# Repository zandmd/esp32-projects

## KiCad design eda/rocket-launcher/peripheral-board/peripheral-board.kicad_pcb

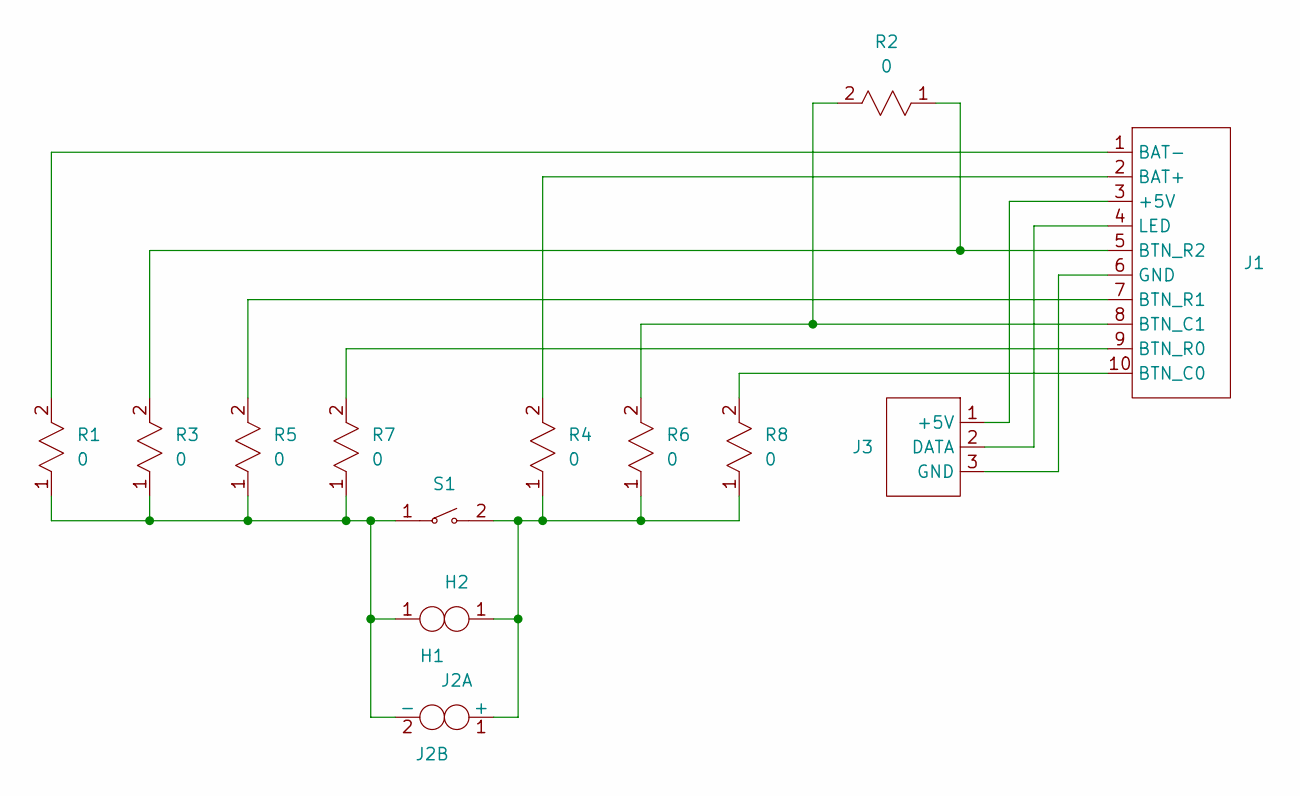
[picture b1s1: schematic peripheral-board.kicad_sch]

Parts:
H1, H2: B076FX76R8
J1: 302-S101
J2: B095WMQ8Y8
J3: B01AG923GI
R1, R2, R3, R4, R5, R6, R7, R8: 0; PASSIVE-NPOL-0805
S1: B07QKFD7Z7

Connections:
unnamed: J1.1 (BAT-), R1.2
unnamed: J1.2 (BAT+), R4.2
unnamed: J1.3 (+5V), J3.1 (+5V)
unnamed: J1.4 (LED), J3.2 (DATA)
unnamed: J1.5 (BTN_R2), R2.1, R3.2
unnamed: J1.6 (GND), J3.3 (GND)
unnamed: J1.7 (BTN_R1), R5.2
unnamed: J1.8 (BTN_C1), R2.2, R6.2
unnamed: J1.9 (BTN_R0), R7.2
unnamed: J1.10 (BTN_C0), R8.2
unnamed: H2.1, J2.1 (+), R4.1, R6.1, R8.1, S1.2
unnamed: H1.1, J2.2 (-), R1.1, R3.1, R5.1, R7.1, S1.1

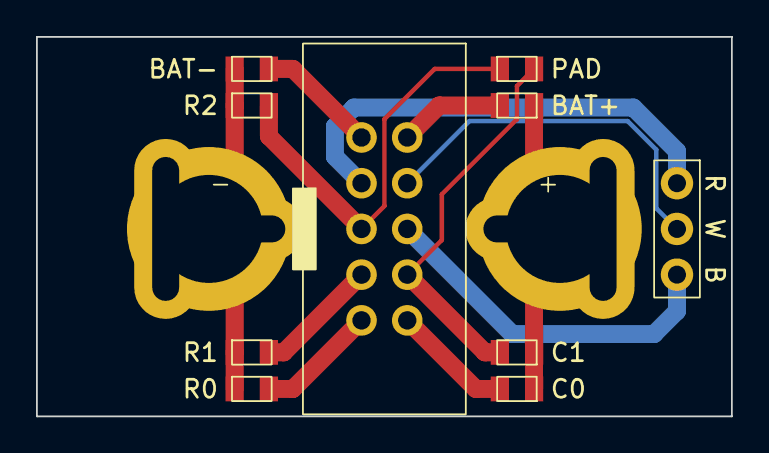
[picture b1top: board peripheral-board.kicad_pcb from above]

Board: 2 copper layers, 38.6 x 21.1 mm, 14 parts (0 on the bottom side), 12 nets.

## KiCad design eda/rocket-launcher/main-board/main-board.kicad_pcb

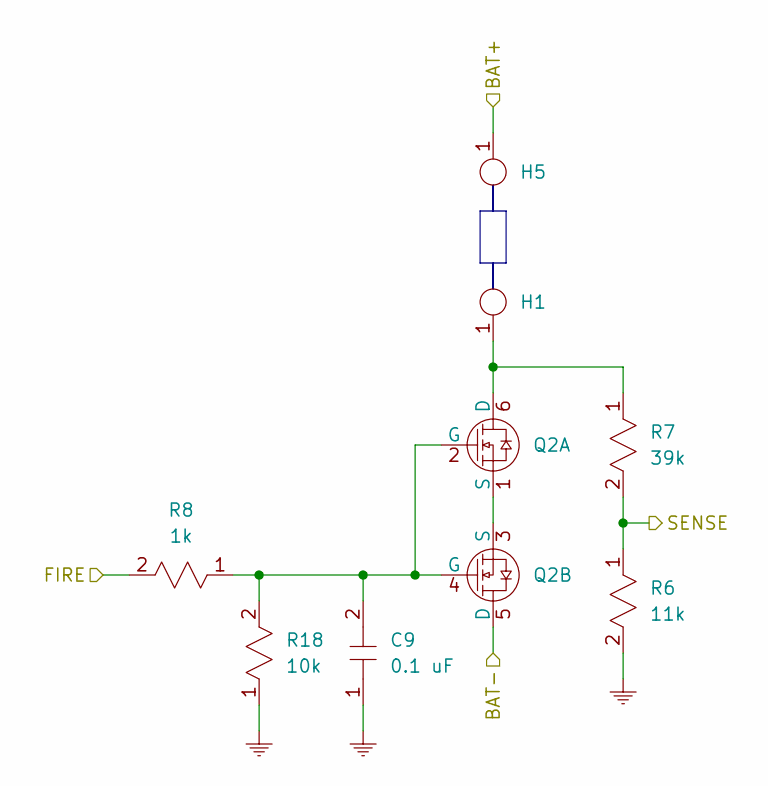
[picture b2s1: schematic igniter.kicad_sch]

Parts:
C9: 0.1 uF; PASSIVE-NPOL-0805
H1, H5: B076FX76R8
Q2: G120N03D32
R6: 11k; PASSIVE-NPOL-0805
R7: 39k; PASSIVE-NPOL-0805
R8: 1k; PASSIVE-NPOL-0805
R18: 10k; PASSIVE-NPOL-0805

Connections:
/+: H5.1; also elsewhere on the board
/-: Q2.5 (D); also elsewhere on the board
/Igniter0/FIRE: R8.2; also elsewhere on the board
/Igniter0/SENSE: R6.1, R7.2; also elsewhere on the board
GND: C9.1, R6.2, R18.1; also elsewhere on the board
unnamed: H1.1, Q2.6 (D), R7.1
unnamed: C9.2, Q2.2 (G), Q2.4 (G), R8.1, R18.2
unnamed: Q2.1 (S), Q2.3 (S)

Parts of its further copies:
C10, C11, C13: 0.1 uF; PASSIVE-NPOL-0805
H2, H3, H4, H6, H7, H8: B076FX76R8
Q3, Q4, Q5: G120N03D32
R9, R12, R15: 11k; PASSIVE-NPOL-0805
R10, R13, R16: 39k; PASSIVE-NPOL-0805
R11, R14, R17: 1k; PASSIVE-NPOL-0805
R19, R20, R21: 10k; PASSIVE-NPOL-0805

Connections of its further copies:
/+: H6.1, H7.1, H8.1; also elsewhere on the board
/-: Q3.5 (D), Q4.5 (D), Q5.5 (D); also elsewhere on the board
/Igniter1/FIRE: R14.2; also elsewhere on the board
/Igniter1/SENSE: R12.1, R13.2; also elsewhere on the board
/Igniter2/FIRE: R11.2; also elsewhere on the board
/Igniter2/SENSE: R9.1, R10.2; also elsewhere on the board
/Igniter3/FIRE: R17.2; also elsewhere on the board
/Igniter3/SENSE: R15.1, R16.2; also elsewhere on the board
GND: C10.1, C11.1, C13.1, R9.2, R12.2, R15.2, R19.1, R20.1, R21.1; also elsewhere on the board
unnamed: H2.1, Q3.6 (D), R10.1
unnamed: C10.2, Q3.2 (G), Q3.4 (G), R11.1, R19.2
unnamed: Q3.1 (S), Q3.3 (S)
unnamed: H3.1, Q4.6 (D), R13.1
unnamed: C11.2, Q4.2 (G), Q4.4 (G), R14.1, R20.2
unnamed: Q4.1 (S), Q4.3 (S)
unnamed: H4.1, Q5.6 (D), R16.1
unnamed: C13.2, Q5.2 (G), Q5.4 (G), R17.1, R21.2
unnamed: Q5.1 (S), Q5.3 (S)

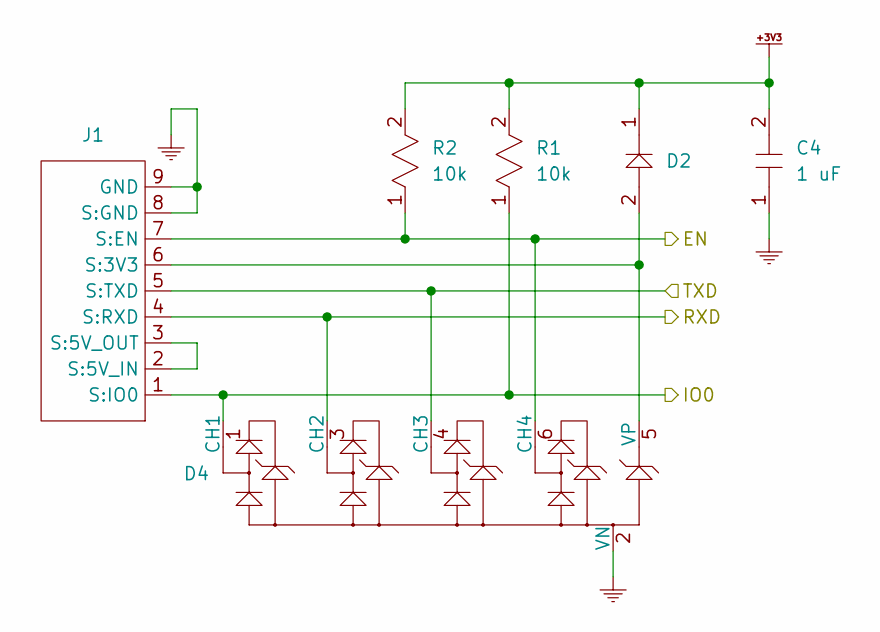
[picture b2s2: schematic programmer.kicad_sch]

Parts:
C4: 1 uF; PASSIVE-NPOL-0805
D2: PASSIVE-POL-0805
D4: CM1293A-04SO
J1: CF25081D0R0-10-NH
R1, R2: 10k; PASSIVE-NPOL-0805

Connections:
+3V3: C4.2, D2.1, R1.2, R2.2; also elsewhere on the board
/Microcontroller/EN: D4.6 (CH4), J1.7 (S:EN), R2.1; also elsewhere on the board
/Microcontroller/IO0: D4.1 (CH1), J1.1 (S:IO0), R1.1; also elsewhere on the board
/Microcontroller/RXD: D4.3 (CH2), J1.4 (S:RXD); also elsewhere on the board
/Microcontroller/TXD: D4.4 (CH3), J1.5 (S:TXD); also elsewhere on the board
GND: C4.1, D4.2 (VN), J1.8 (S:GND), J1.9 (GND); also elsewhere on the board
unnamed: D2.2, D4.5 (VP), J1.6 (S:3V3)
unnamed: J1.2 (S:5V_IN), J1.3 (S:5V_OUT)

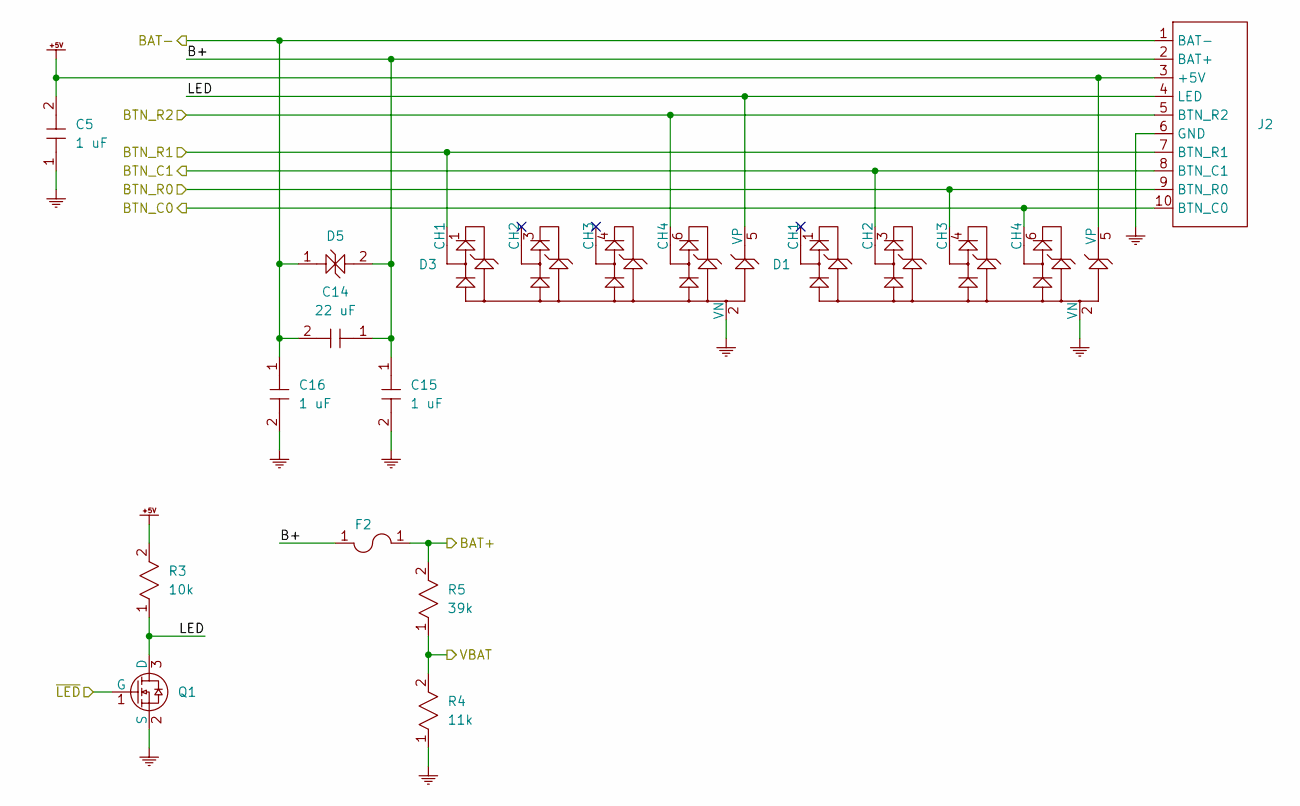
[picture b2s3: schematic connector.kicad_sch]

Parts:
C5, C15, C16: 1 uF; PASSIVE-NPOL-0805
C14: 22 uF; PASSIVE-NPOL-0805
D1, D3: CM1293A-04SO
D5: SMAJ15CA
F2, F3: 3586KTR
J2: 302-S101
Q1: BSS816NWH6327XTSA1
R3: 10k; PASSIVE-NPOL-0805
R4: 11k; PASSIVE-NPOL-0805
R5: 39k; PASSIVE-NPOL-0805

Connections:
+5V: C5.2, D1.5 (VP), J2.3 (+5V), R3.2; also elsewhere on the board
/+: F3.1, R5.2; also elsewhere on the board
/-: C14.2, C16.1, D5.1, J2.1 (BAT-); also elsewhere on the board
/Connector/B+: C14.1, C15.1, D5.2, F2.1, J2.2 (BAT+)
/Connector/BTN_C0: D1.6 (CH4), J2.10 (BTN_C0); also elsewhere on the board
/Connector/BTN_C1: D1.3 (CH2), J2.8 (BTN_C1); also elsewhere on the board
/Connector/BTN_R0: D1.4 (CH3), J2.9 (BTN_R0); also elsewhere on the board
/Connector/BTN_R1: D3.1 (CH1), J2.7 (BTN_R1); also elsewhere on the board
/Connector/BTN_R2: D3.6 (CH4), J2.5 (BTN_R2); also elsewhere on the board
/Connector/LED: D3.5 (VP), J2.4 (LED), Q1.3 (D), R3.1
/Connector/VBAT: R4.2, R5.1; also elsewhere on the board
/Connector/~LED: Q1.1 (G); also elsewhere on the board
GND: C5.1, C15.2, C16.2, D1.2 (VN), D3.2 (VN), J2.6 (GND), Q1.2 (S), R4.1; also elsewhere on the board

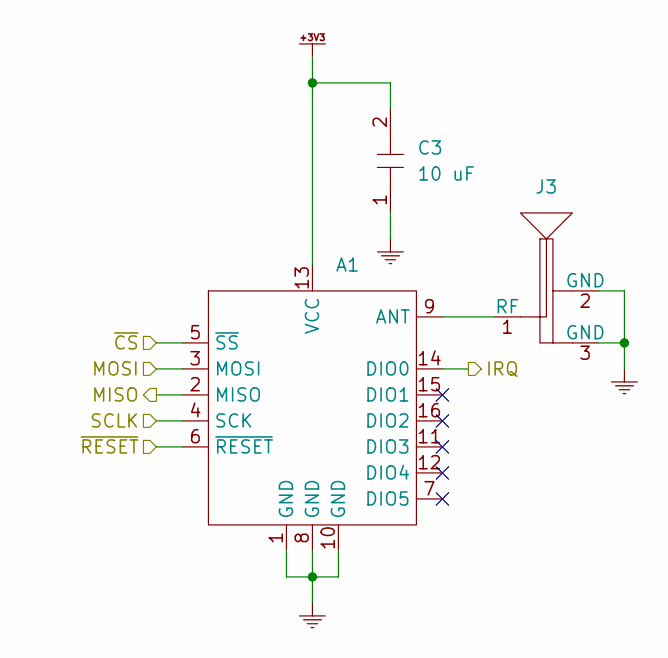
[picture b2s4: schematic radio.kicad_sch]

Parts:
A1: 5684
C3: 10 uF; PASSIVE-NPOL-0805
J3: 2337019-1

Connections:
+3V3: A1.13 (VCC), C3.2; also elsewhere on the board
/Microcontroller/MISO: A1.2 (MISO); also elsewhere on the board
/Microcontroller/MOSI: A1.3 (MOSI); also elsewhere on the board
/Microcontroller/RFM_IRQ: A1.14 (DIO0); also elsewhere on the board
/Microcontroller/SCLK: A1.4 (SCK); also elsewhere on the board
/Microcontroller/~CS: A1.5 (~SS); also elsewhere on the board
/Microcontroller/~RFM_RST: A1.6 (~RESET); also elsewhere on the board
GND: A1.1 (GND), A1.8 (GND), A1.10 (GND), C3.1, J3.2 (GND), J3.3 (GND); also elsewhere on the board
unnamed: A1.9 (ANT), J3.1 (RF)

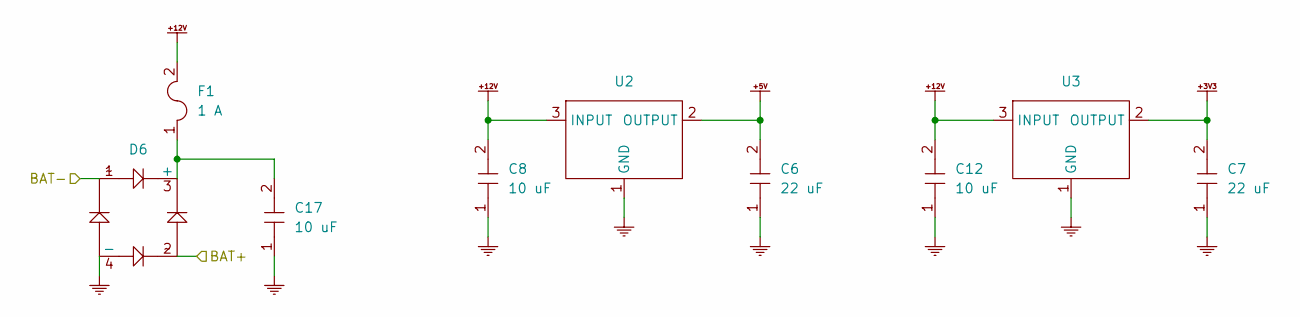
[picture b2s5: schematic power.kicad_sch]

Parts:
C6, C7: 22 uF; PASSIVE-NPOL-0805
C8, C12, C17: 10 uF; PASSIVE-NPOL-0805
D6: MB14S
F1: 1 A; PASSIVE-NPOL-1206
U2: AZ1117IH-5.0TRG1
U3: AZ1117IH-3.3TRG1

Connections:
+3V3: C7.2, U3.2 (OUTPUT); also elsewhere on the board
+5V: C6.2, U2.2 (OUTPUT); also elsewhere on the board
+12V: C8.2, C12.2, F1.2, U2.3 (INPUT), U3.3 (INPUT)
/+: D6.2; also elsewhere on the board
/-: D6.1; also elsewhere on the board
GND: C6.1, C7.1, C8.1, C12.1, C17.1, D6.4 (-), U2.1 (GND), U3.1 (GND); also elsewhere on the board
unnamed: C17.2, D6.3 (+), F1.1

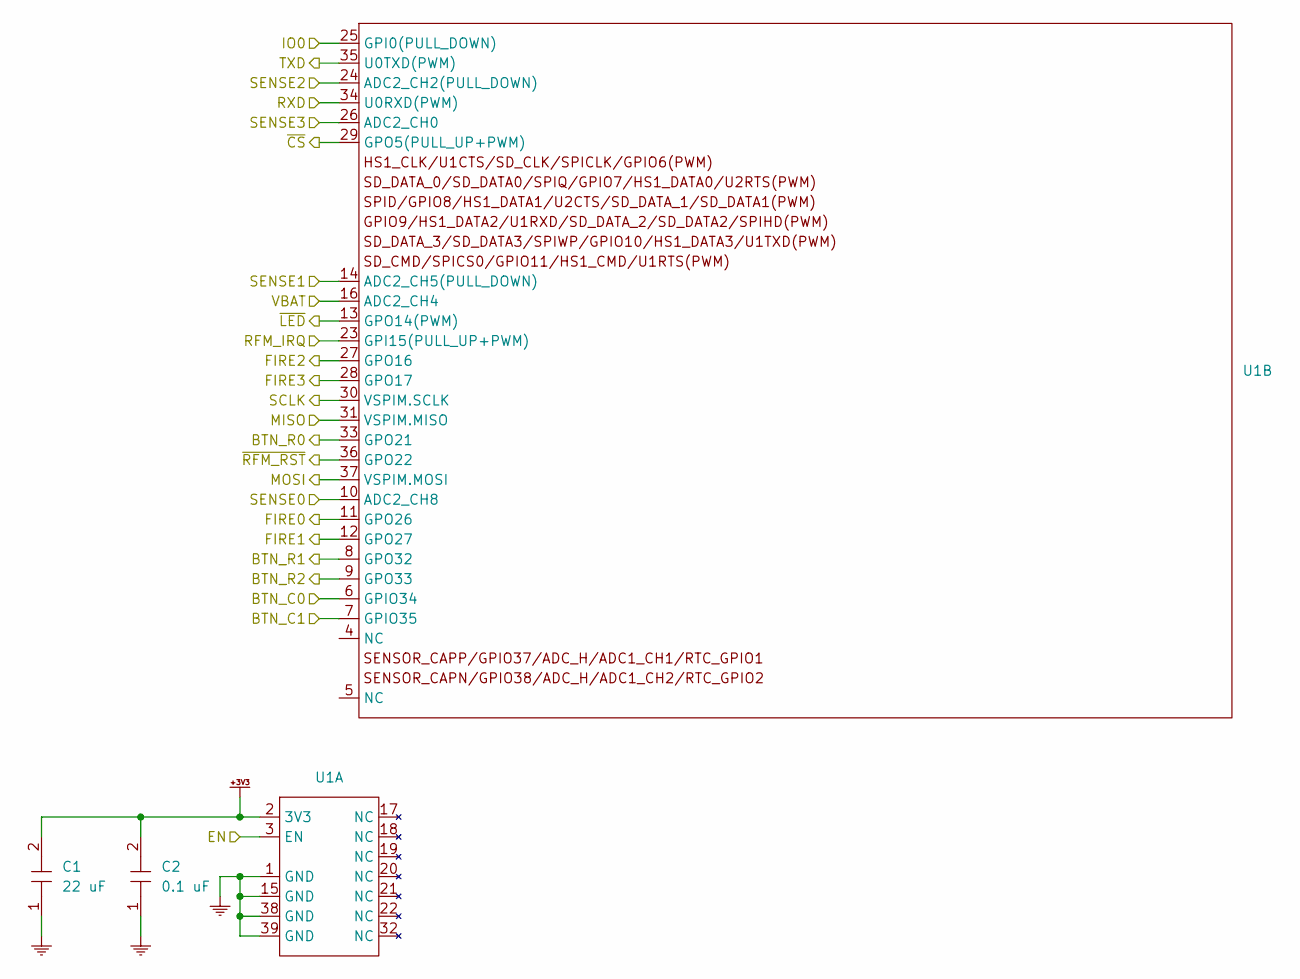
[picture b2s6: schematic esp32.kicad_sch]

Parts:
C1: 22 uF; PASSIVE-NPOL-0805
C2: 0.1 uF; PASSIVE-NPOL-0805
U1: ESP32-WROOM-32E-N4

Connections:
+3V3: C1.2, C2.2, U1.2 (3V3); also elsewhere on the board
/Connector/BTN_C0: U1.6 (GPIO34); also elsewhere on the board
/Connector/BTN_C1: U1.7 (GPIO35); also elsewhere on the board
/Connector/BTN_R0: U1.33 (GPO21); also elsewhere on the board
/Connector/BTN_R1: U1.8 (GPO32); also elsewhere on the board
/Connector/BTN_R2: U1.9 (GPO33); also elsewhere on the board
/Connector/VBAT: U1.16 (ADC2_CH4); also elsewhere on the board
/Connector/~LED: U1.13 (GPO14(PWM)); also elsewhere on the board
/Igniter0/FIRE: U1.11 (GPO26); also elsewhere on the board
/Igniter0/SENSE: U1.10 (ADC2_CH8); also elsewhere on the board
/Igniter1/FIRE: U1.12 (GPO27); also elsewhere on the board
/Igniter1/SENSE: U1.14 (ADC2_CH5(PULL_DOWN)); also elsewhere on the board
/Igniter2/FIRE: U1.27 (GPO16); also elsewhere on the board
/Igniter2/SENSE: U1.24 (ADC2_CH2(PULL_DOWN)); also elsewhere on the board
/Igniter3/FIRE: U1.28 (GPO17); also elsewhere on the board
/Igniter3/SENSE: U1.26 (ADC2_CH0); also elsewhere on the board
/Microcontroller/EN: U1.3 (EN); also elsewhere on the board
/Microcontroller/IO0: U1.25 (GPI0(PULL_DOWN)); also elsewhere on the board
/Microcontroller/MISO: U1.31 (VSPIM.MISO); also elsewhere on the board
/Microcontroller/MOSI: U1.37 (VSPIM.MOSI); also elsewhere on the board
/Microcontroller/RFM_IRQ: U1.23 (GPI15(PULL_UP+PWM)); also elsewhere on the board
/Microcontroller/RXD: U1.34 (U0RXD(PWM)); also elsewhere on the board
/Microcontroller/SCLK: U1.30 (VSPIM.SCLK); also elsewhere on the board
/Microcontroller/TXD: U1.35 (U0TXD(PWM)); also elsewhere on the board
/Microcontroller/~CS: U1.29 (GPO5(PULL_UP+PWM)); also elsewhere on the board
/Microcontroller/~RFM_RST: U1.36 (GPO22); also elsewhere on the board
GND: C1.1, C2.1, U1.1 (GND), U1.15 (GND), U1.38 (GND), U1.39 (GND); also elsewhere on the board

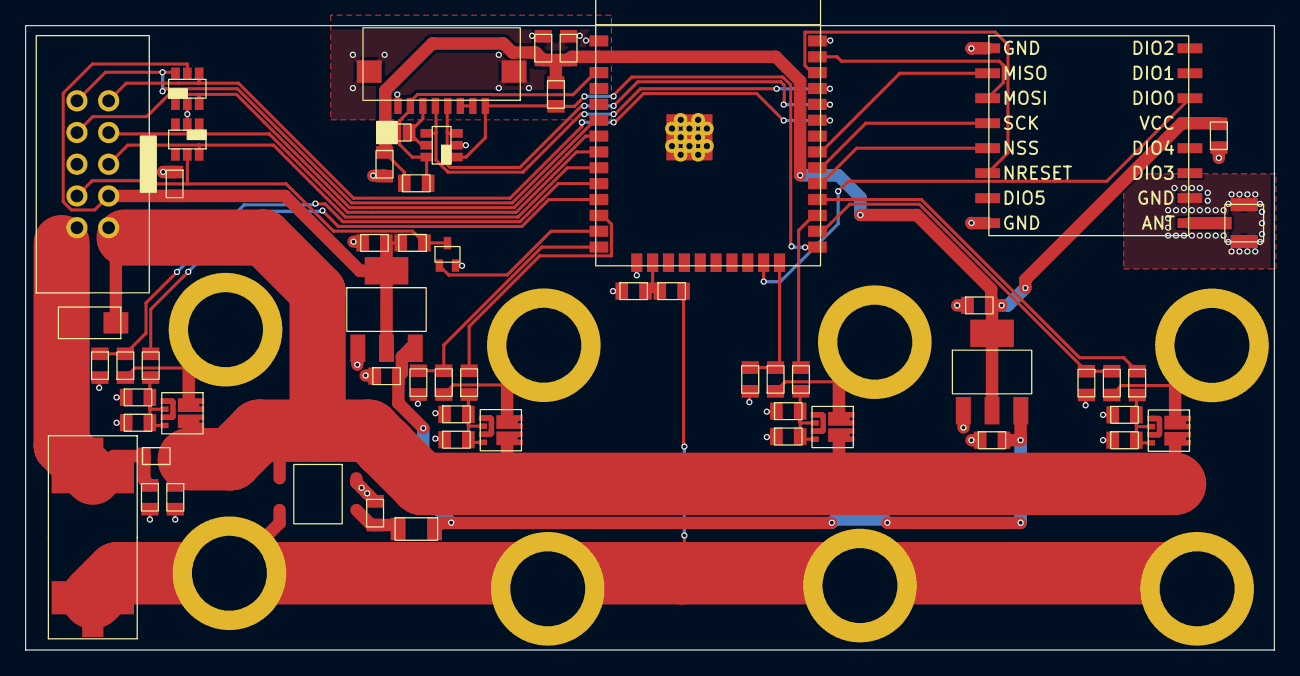
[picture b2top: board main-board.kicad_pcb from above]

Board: 2 copper layers, 100.0 x 50.0 mm, 67 parts (0 on the bottom side), 49 nets.

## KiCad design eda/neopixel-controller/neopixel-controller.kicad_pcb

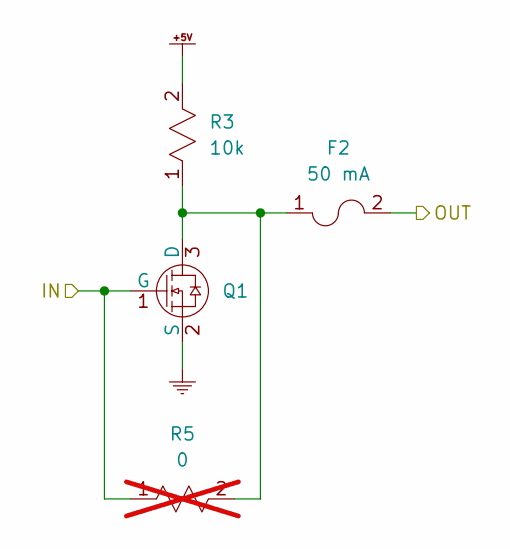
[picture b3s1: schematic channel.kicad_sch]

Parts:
F2: 50 mA; PASSIVE-NPOL-1206
Q1: BSS816NWH6327XTSA1
R3: 10k; PASSIVE-NPOL-0805
R5: 0; PASSIVE-NPOL-0805; not fitted

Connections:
+5V: R3.2; also elsewhere on the board
/Channel 0/IN: Q1.1 (G), R5.1; also elsewhere on the board
/Channel 0/OUT: F2.2; also elsewhere on the board
GND: Q1.2 (S); also elsewhere on the board
unnamed: F2.1, Q1.3 (D), R3.1, R5.2

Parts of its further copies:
F3, F4, F5, F6, F7, F8, F9: 50 mA; PASSIVE-NPOL-1206
Q2, Q3, Q4, Q5, Q6, Q7, Q8: BSS816NWH6327XTSA1
R4, R7, R9, R11, R13, R17, R18: 10k; PASSIVE-NPOL-0805
R6, R8, R10, R14, R15, R19, R20: 0; PASSIVE-NPOL-0805; not fitted

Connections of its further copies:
+5V: R4.2, R7.2, R9.2, R11.2, R13.2, R17.2, R18.2; also elsewhere on the board
/Channel 1/IN: Q2.1 (G), R6.1; also elsewhere on the board
/Channel 1/OUT: F3.2; also elsewhere on the board
/Channel 2/IN: Q4.1 (G), R10.1; also elsewhere on the board
/Channel 2/OUT: F4.2; also elsewhere on the board
/Channel 3/IN: Q3.1 (G), R8.1; also elsewhere on the board
/Channel 3/OUT: F5.2; also elsewhere on the board
/Channel 4/IN: Q6.1 (G), R15.1; also elsewhere on the board
/Channel 4/OUT: F6.2; also elsewhere on the board
/Channel 5/IN: Q5.1 (G), R14.1; also elsewhere on the board
/Channel 5/OUT: F7.2; also elsewhere on the board
/Channel 6/IN: Q8.1 (G), R20.1; also elsewhere on the board
/Channel 6/OUT: F8.2; also elsewhere on the board
/Channel 7/IN: Q7.1 (G), R19.1; also elsewhere on the board
/Channel 7/OUT: F9.2; also elsewhere on the board
GND: Q2.2 (S), Q3.2 (S), Q4.2 (S), Q5.2 (S), Q6.2 (S), Q7.2 (S), Q8.2 (S); also elsewhere on the board
unnamed: F3.1, Q2.3 (D), R4.1, R6.2
unnamed: F5.1, Q3.3 (D), R7.1, R8.2
unnamed: F4.1, Q4.3 (D), R9.1, R10.2
unnamed: F7.1, Q5.3 (D), R11.1, R14.2
unnamed: F6.1, Q6.3 (D), R13.1, R15.2
unnamed: F9.1, Q7.3 (D), R17.1, R19.2
unnamed: F8.1, Q8.3 (D), R18.1, R20.2

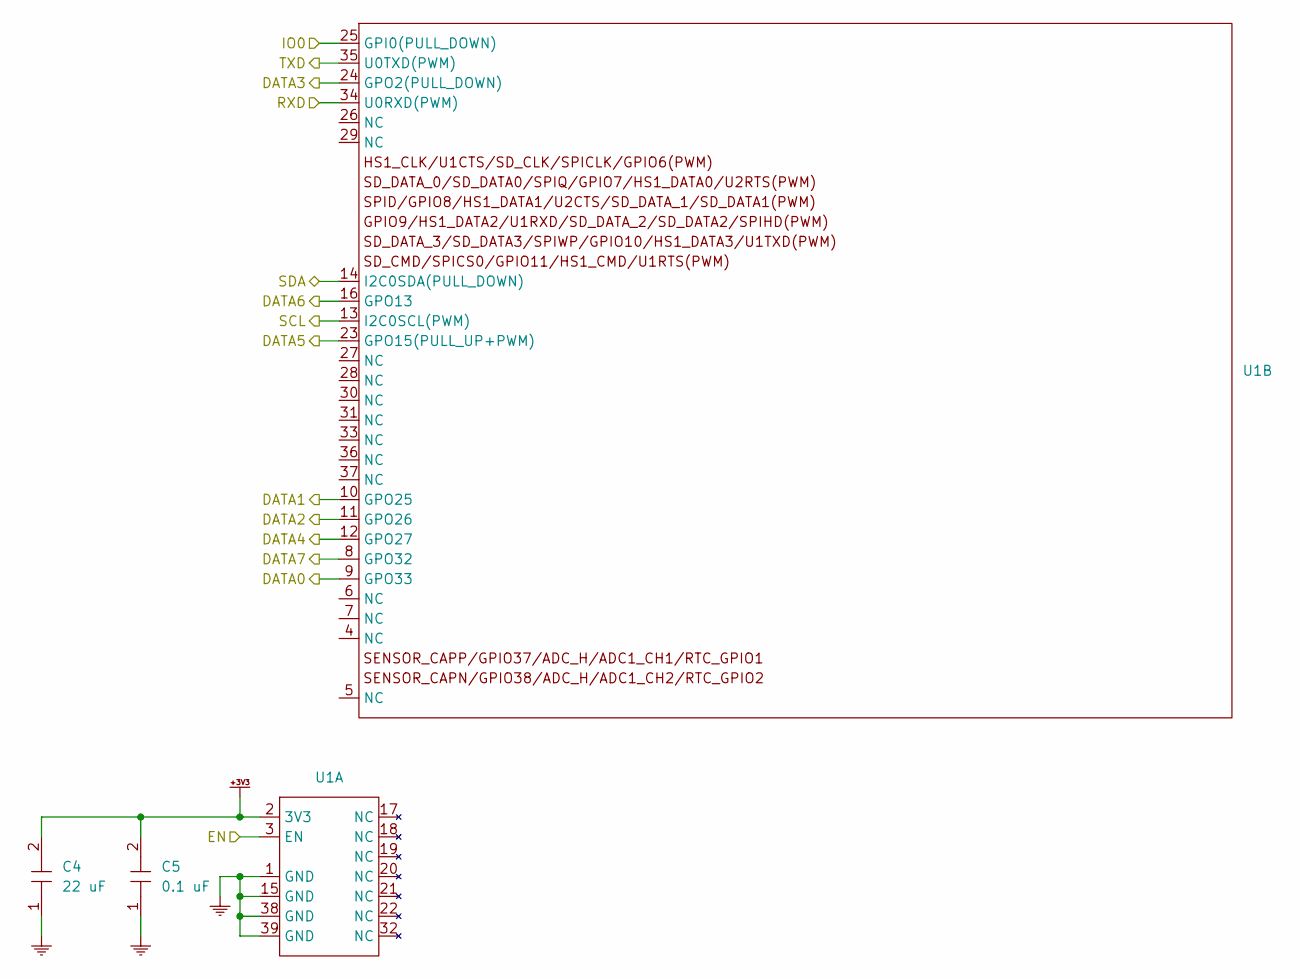
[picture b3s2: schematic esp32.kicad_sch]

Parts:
C4: 22 uF; PASSIVE-NPOL-0805
C5: 0.1 uF; PASSIVE-NPOL-0805
U1: ESP32-WROOM-32E-N4

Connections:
+3V3: C4.2, C5.2, U1.2 (3V3); also elsewhere on the board
/Channel 0/IN: U1.9 (GPO33); also elsewhere on the board
/Channel 1/IN: U1.10 (GPO25); also elsewhere on the board
/Channel 2/IN: U1.11 (GPO26); also elsewhere on the board
/Channel 3/IN: U1.24 (GPO2(PULL_DOWN)); also elsewhere on the board
/Channel 4/IN: U1.12 (GPO27); also elsewhere on the board
/Channel 5/IN: U1.23 (GPO15(PULL_UP+PWM)); also elsewhere on the board
/Channel 6/IN: U1.16 (GPO13); also elsewhere on the board
/Channel 7/IN: U1.8 (GPO32); also elsewhere on the board
/Microcontroller/EN: U1.3 (EN); also elsewhere on the board
/Microcontroller/IO0: U1.25 (GPI0(PULL_DOWN)); also elsewhere on the board
/Microcontroller/RXD: U1.34 (U0RXD(PWM)); also elsewhere on the board
/Microcontroller/SCL: U1.13 (I2C0SCL(PWM)); also elsewhere on the board
/Microcontroller/SDA: U1.14 (I2C0SDA(PULL_DOWN)); also elsewhere on the board
/Microcontroller/TXD: U1.35 (U0TXD(PWM)); also elsewhere on the board
GND: C4.1, C5.1, U1.1 (GND), U1.15 (GND), U1.38 (GND), U1.39 (GND); also elsewhere on the board

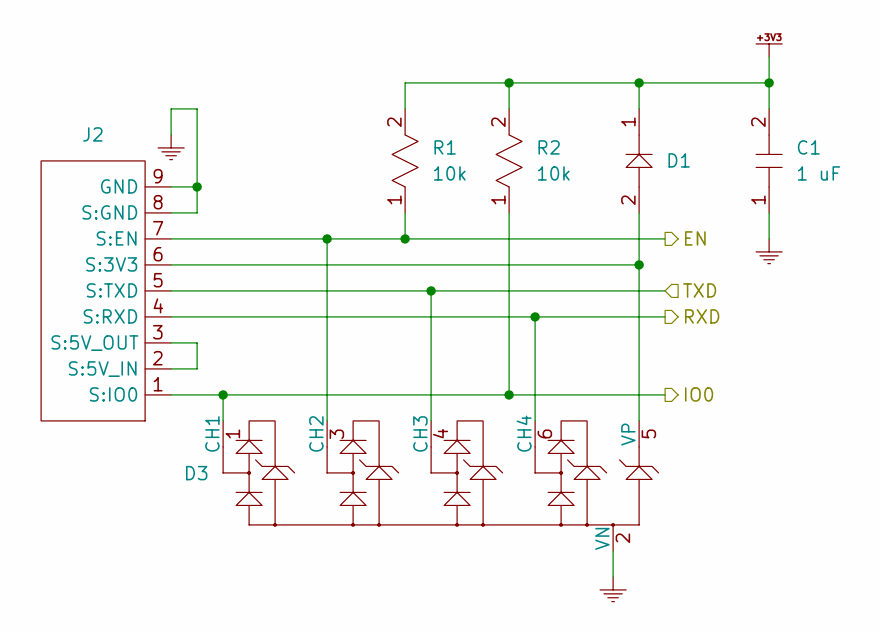
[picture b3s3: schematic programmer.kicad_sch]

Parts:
C1: 1 uF; PASSIVE-NPOL-0805
D1: PASSIVE-POL-0805
D3: CM1293A-04SO
J2: CF25081D0R0-10-NH
R1, R2: 10k; PASSIVE-NPOL-0805

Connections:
+3V3: C1.2, D1.1, R1.2, R2.2; also elsewhere on the board
/Microcontroller/EN: D3.3 (CH2), J2.7 (S:EN), R1.1; also elsewhere on the board
/Microcontroller/IO0: D3.1 (CH1), J2.1 (S:IO0), R2.1; also elsewhere on the board
/Microcontroller/RXD: D3.6 (CH4), J2.4 (S:RXD); also elsewhere on the board
/Microcontroller/TXD: D3.4 (CH3), J2.5 (S:TXD); also elsewhere on the board
GND: C1.1, D3.2 (VN), J2.8 (S:GND), J2.9 (GND); also elsewhere on the board
unnamed: D1.2, D3.5 (VP), J2.6 (S:3V3)
unnamed: J2.2 (S:5V_IN), J2.3 (S:5V_OUT)

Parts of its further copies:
R4: 10k; PASSIVE-NPOL-0805

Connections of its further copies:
+5V: R4.2; also elsewhere on the board
unnamed 30: R4.1; also elsewhere on the board

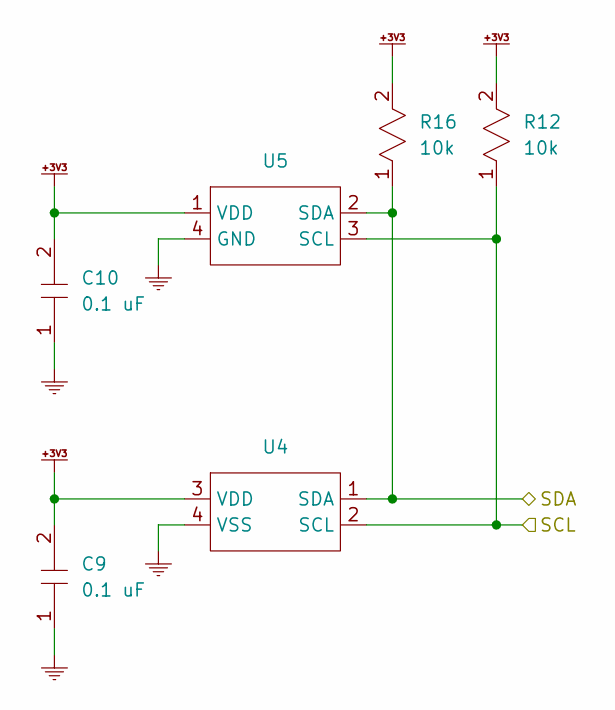
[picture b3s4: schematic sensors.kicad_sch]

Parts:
C9, C10: 0.1 uF; PASSIVE-NPOL-0805
R12, R16: 10k; PASSIVE-NPOL-0805
U4: SHT40-BD1B-R3
U5: MS563702BA03-50

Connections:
+3V3: C9.2, C10.2, R12.2, R16.2, U4.3 (VDD), U5.1 (VDD); also elsewhere on the board
/Microcontroller/SCL: R12.1, U4.2 (SCL), U5.3 (SCL); also elsewhere on the board
/Microcontroller/SDA: R16.1, U4.1 (SDA), U5.2 (SDA); also elsewhere on the board
GND: C9.1, C10.1, U4.4 (VSS), U5.4 (GND); also elsewhere on the board

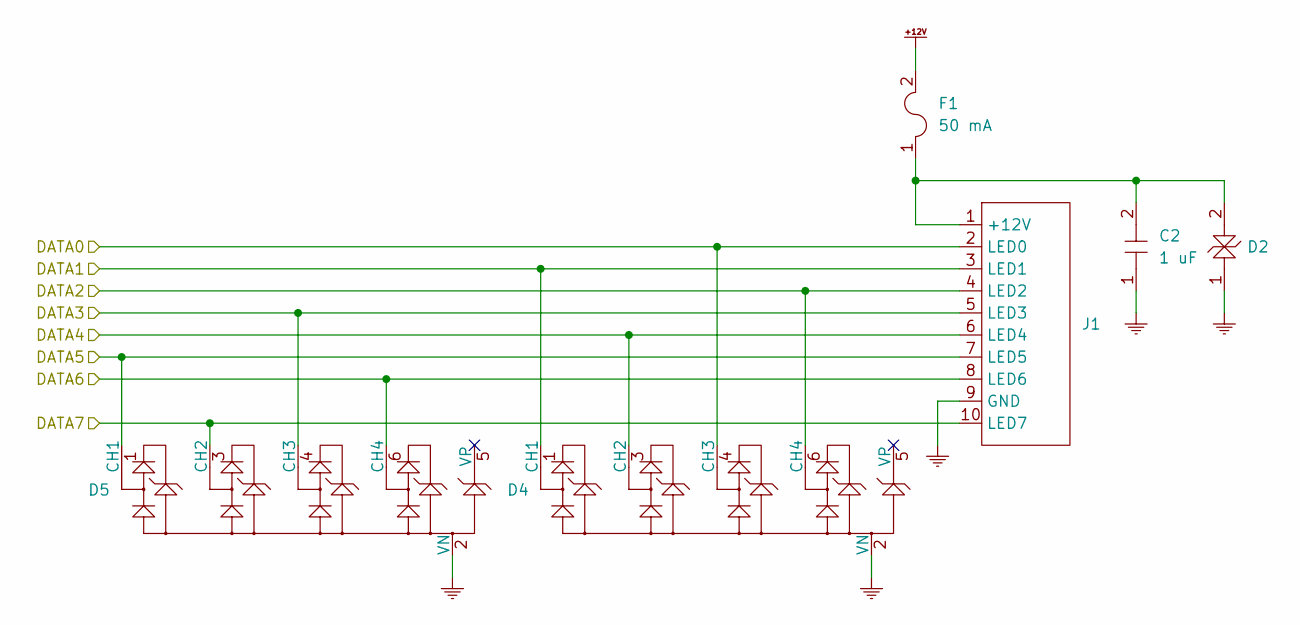
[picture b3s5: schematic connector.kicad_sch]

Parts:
C2: 1 uF; PASSIVE-NPOL-0805
D2: SMAJ15CA
D4, D5: CM1293A-04SO
F1: 50 mA; PASSIVE-NPOL-1206
J1: 302-S101

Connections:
+12V: F1.2; also elsewhere on the board
/Channel 0/OUT: D4.4 (CH3), J1.2 (LED0); also elsewhere on the board
/Channel 1/OUT: D4.1 (CH1), J1.3 (LED1); also elsewhere on the board
/Channel 2/OUT: D4.6 (CH4), J1.4 (LED2); also elsewhere on the board
/Channel 3/OUT: D5.4 (CH3), J1.5 (LED3); also elsewhere on the board
/Channel 4/OUT: D4.3 (CH2), J1.6 (LED4); also elsewhere on the board
/Channel 5/OUT: D5.1 (CH1), J1.7 (LED5); also elsewhere on the board
/Channel 6/OUT: D5.6 (CH4), J1.8 (LED6); also elsewhere on the board
/Channel 7/OUT: D5.3 (CH2), J1.10 (LED7); also elsewhere on the board
GND: C2.1, D2.1, D4.2 (VN), D5.2 (VN), J1.9 (GND); also elsewhere on the board
unnamed: C2.2, D2.2, F1.1, J1.1 (+12V)

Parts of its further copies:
F3, F4, F5, F6, F7, F8: 50 mA; PASSIVE-NPOL-1206

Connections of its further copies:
/Channel 1/OUT: F3.2; also elsewhere on the board
/Channel 2/OUT: F4.2; also elsewhere on the board
/Channel 3/OUT: F5.2; also elsewhere on the board
/Channel 4/OUT: F6.2; also elsewhere on the board
/Channel 5/OUT: F7.2; also elsewhere on the board
/Channel 6/OUT: F8.2; also elsewhere on the board
unnamed 30: F3.1; also elsewhere on the board
unnamed 31: F5.1; also elsewhere on the board
unnamed 32: F4.1; also elsewhere on the board
unnamed 33: F7.1; also elsewhere on the board
unnamed 34: F6.1; also elsewhere on the board
unnamed 36: F8.1; also elsewhere on the board

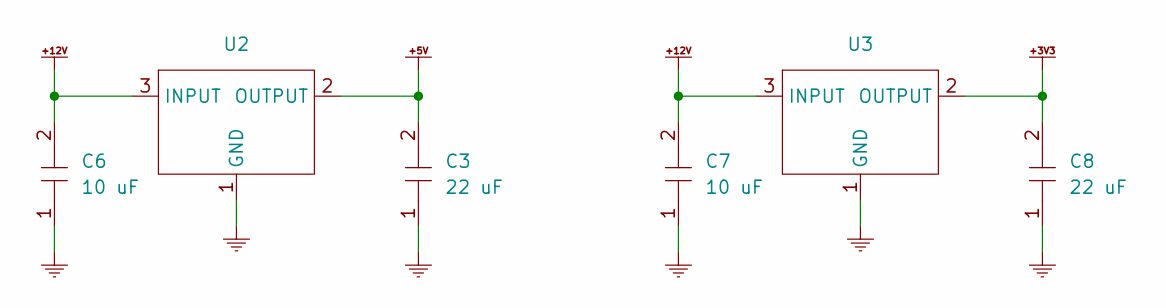
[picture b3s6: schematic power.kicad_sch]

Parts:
C3, C8: 22 uF; PASSIVE-NPOL-0805
C6, C7: 10 uF; PASSIVE-NPOL-0805
U2: AZ1117IH-5.0TRG1
U3: AZ1117IH-3.3TRG1

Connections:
+3V3: C8.2, U3.2 (OUTPUT); also elsewhere on the board
+5V: C3.2, U2.2 (OUTPUT); also elsewhere on the board
+12V: C6.2, C7.2, U2.3 (INPUT), U3.3 (INPUT); also elsewhere on the board
GND: C3.1, C6.1, C7.1, C8.1, U2.1 (GND), U3.1 (GND); also elsewhere on the board

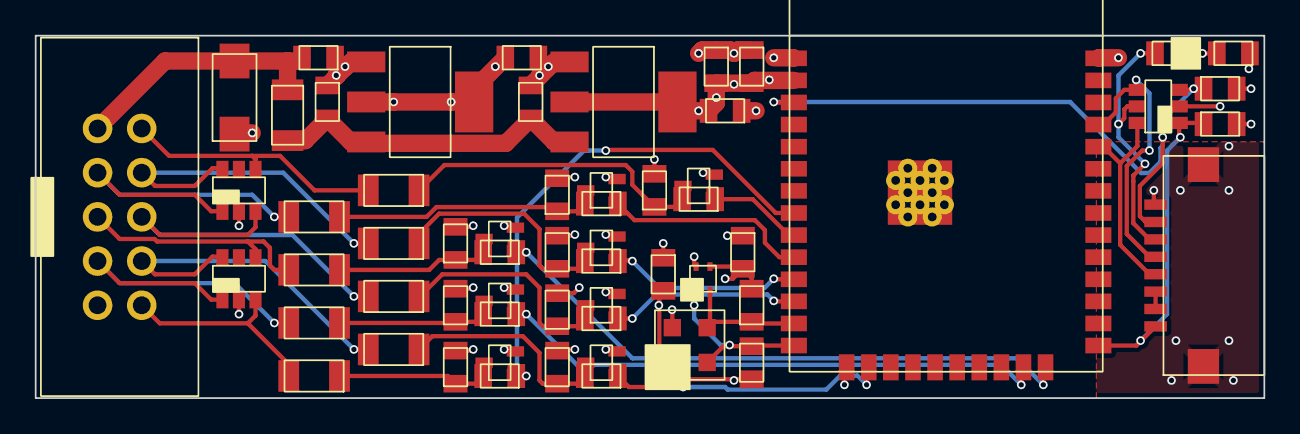
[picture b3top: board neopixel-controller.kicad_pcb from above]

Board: 4 copper layers, 70.6 x 20.8 mm, 59 parts (0 on the bottom side), 37 nets.

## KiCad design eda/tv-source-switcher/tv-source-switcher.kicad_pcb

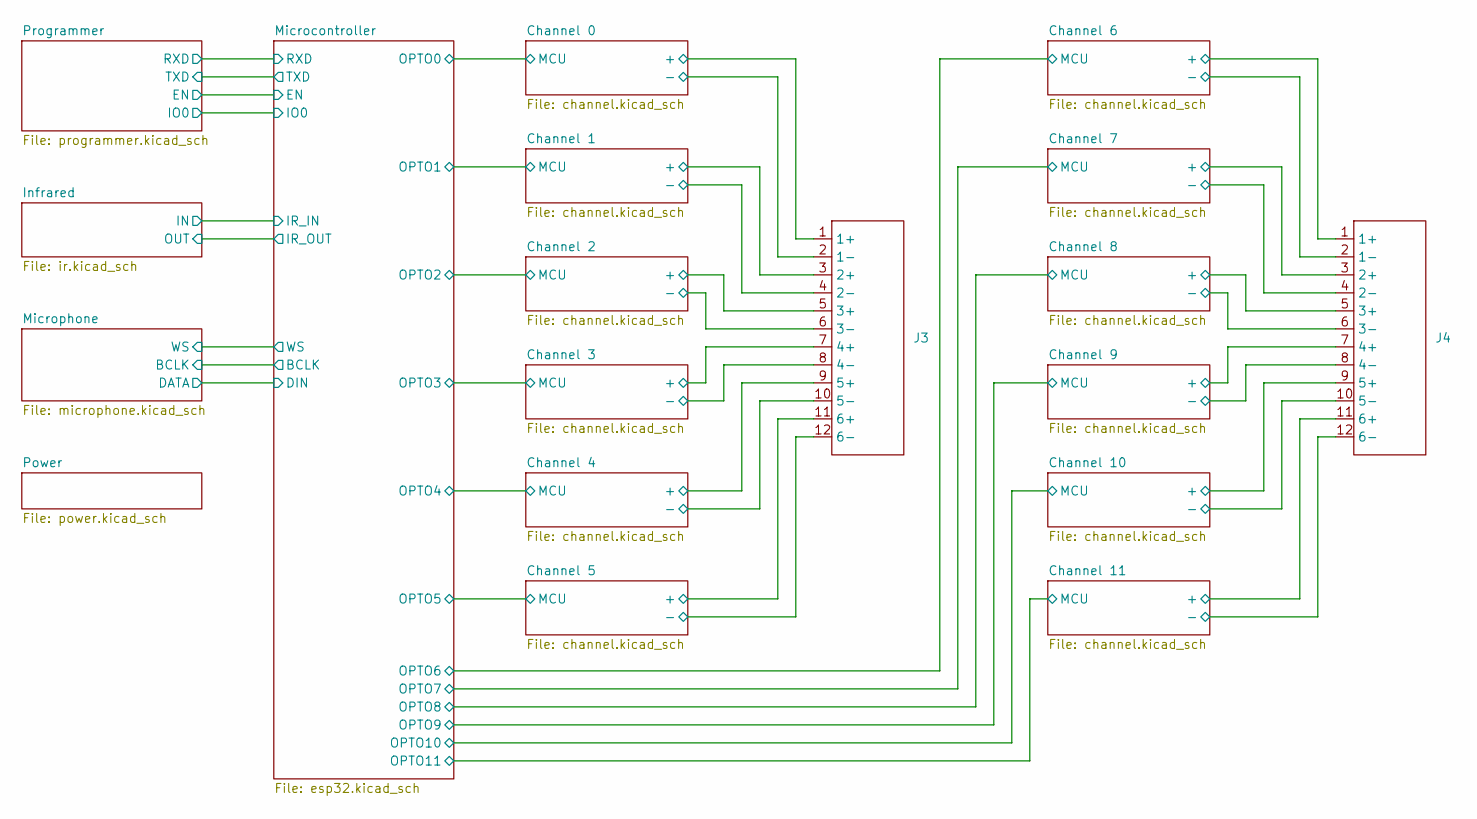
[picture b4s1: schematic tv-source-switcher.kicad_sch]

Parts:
J3, J4: OSTVN12A150

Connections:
/Channel 1/+: J3.3 (2+); also elsewhere on the board
/Channel 1/-: J3.4 (2-); also elsewhere on the board
/Channel 2/+: J3.5 (3+); also elsewhere on the board
/Channel 2/-: J3.6 (3-); also elsewhere on the board
/Channel 3/+: J3.7 (4+); also elsewhere on the board
/Channel 3/-: J3.8 (4-); also elsewhere on the board
/Channel 4/+: J3.9 (5+); also elsewhere on the board
/Channel 4/-: J3.10 (5-); also elsewhere on the board
/Channel 5/+: J3.11 (6+); also elsewhere on the board
/Channel 5/-: J3.12 (6-); also elsewhere on the board
/Channel 6/+: J4.1 (1+); also elsewhere on the board
/Channel 6/-: J4.2 (1-); also elsewhere on the board
/Channel 7/+: J4.3 (2+); also elsewhere on the board
/Channel 7/-: J4.4 (2-); also elsewhere on the board
/Channel 8/+: J4.5 (3+); also elsewhere on the board
/Channel 8/-: J4.6 (3-); also elsewhere on the board
/Channel 9/+: J4.7 (4+); also elsewhere on the board
/Channel 9/-: J4.8 (4-); also elsewhere on the board
/Channel 10/+: J4.9 (5+); also elsewhere on the board
/Channel 10/-: J4.10 (5-); also elsewhere on the board
